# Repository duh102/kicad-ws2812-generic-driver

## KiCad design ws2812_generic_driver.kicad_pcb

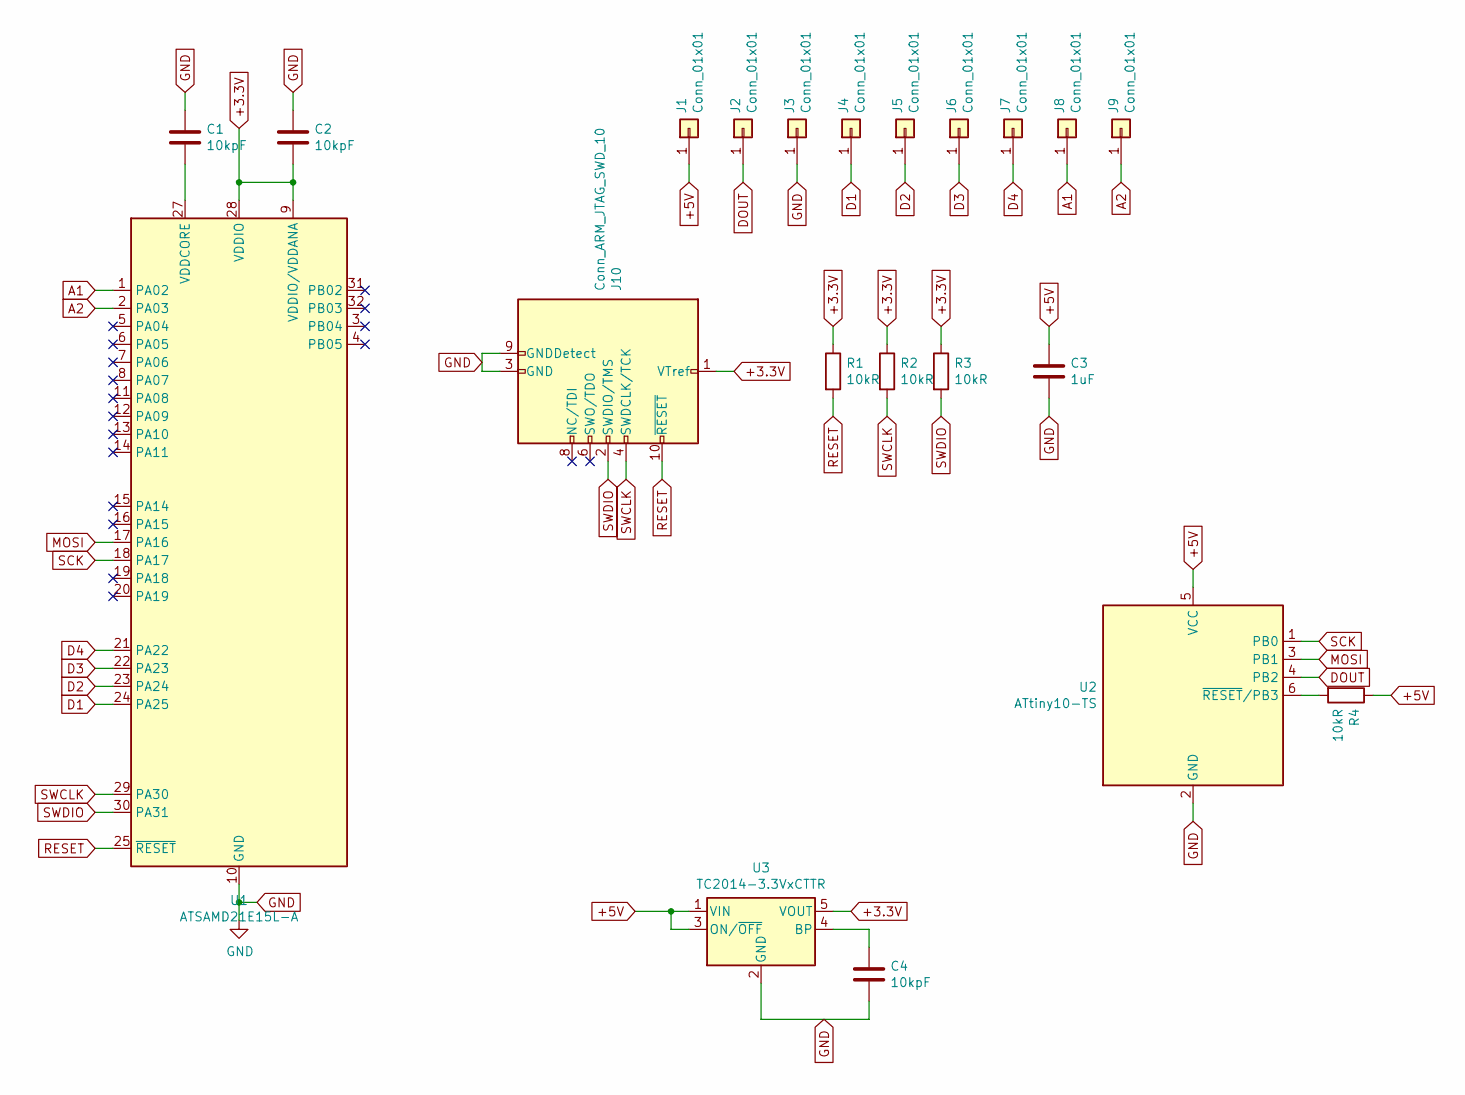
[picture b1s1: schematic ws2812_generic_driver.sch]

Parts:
C1, C2, C4: 10kpF; C_0603_1608Metric
C3: 1uF; C_0805_2012Metric
J1, J2, J3, J4, J5, J6, J7, J8, J9: Conn_01x01; TestPoint_Pad_1.5x1.5mm
J10: Conn_ARM_JTAG_SWD_10; PinHeader_2x05_P1.27mm_Vertical
R1, R2, R3, R4: 10kR; R_0805_2012Metric
U1: ATSAMD21E15L-A; TQFP-32_7x7mm_P0.8mm
U2: ATtiny10-TS; SOT-23-6
U3: TC2014-3.3VxCTTR; SOT-23-5

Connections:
+3.3V: C2.2, J10.1 (VTref), R1.1, R2.1, R3.1, U1.9 (VDDIO/VDDANA), U1.28 (VDDIO), U3.5 (VOUT)
+5V: C3.1, J1.1, R4.1, U2.5 (VCC), U3.1 (VIN), U3.3 (ON/~OFF~)
A1: J8.1, U1.1 (PA02)
A2: J9.1, U1.2 (PA03)
D1: J4.1, U1.24 (PA25)
D2: J5.1, U1.23 (PA24)
D3: J6.1, U1.22 (PA23)
D4: J7.1, U1.21 (PA22)
DOUT: J2.1, U2.4 (PB2)
GND: C1.1, C2.1, C3.2, C4.2, J3.1, J10.3 (GND), J10.5 (GND), J10.9 (GNDDetect), U1.10 (GND), U1.26 (GND), U2.2 (GND), U3.2 (GND)
MOSI: U1.17 (PA16), U2.3 (PB1)
unnamed: C1.2, U1.27 (VDDCORE)
unnamed: C4.1, U3.4 (BP)
unnamed: R4.2, U2.6 (~RESET~/PB3)
RESET: J10.10 (~RESET~), R1.2, U1.25 (~RESET)
SCK: U1.18 (PA17), U2.1 (PB0)
SWCLK: J10.4 (SWDCLK/TCK), R2.2, U1.29 (PA30)
SWDIO: J10.2 (SWDIO/TMS), R3.2, U1.30 (PA31)

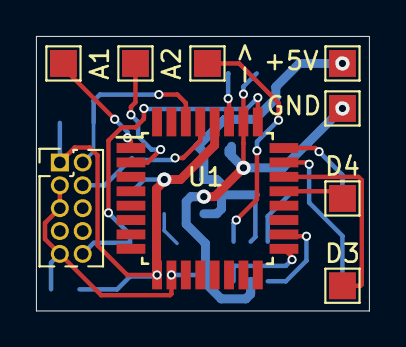
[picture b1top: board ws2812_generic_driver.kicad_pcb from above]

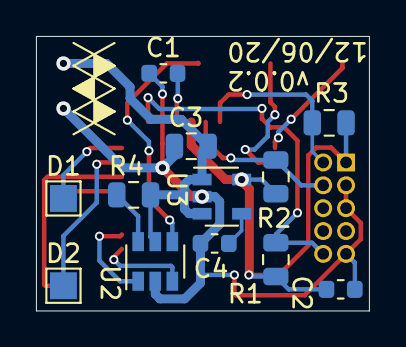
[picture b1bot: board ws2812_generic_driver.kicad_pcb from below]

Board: 2 copper layers, 18.5 x 15.2 mm, 21 parts (12 on the bottom side), 18 nets.

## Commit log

2020-11-14 Add attiny10 hardware spi->ws2812 support
2020-11-14 Move around silkscreen
2020-12-06 Fix core overvoltage problem
2020-12-07 Minor fixes
